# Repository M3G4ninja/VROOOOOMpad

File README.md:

### VROOOOMpad

VROOOOMpad is a 9-key macropad with a rotary encoder, an OLED Display. It also has 16 SK6812 LEDs, and uses KMK firmware.

It contains an implementation of every common part, and achieves my goal of being able to understand and use some of the comon inputs and outputs associated with a macropad.

**Features:**

-   Designed for a custom 3D printed case.
    
-   128x32 OLED Display
    
-   EC11 Rotary encoder for whatever you want
    
-   16 SK6812 RGB LEDs for per-key lighting and effects.
    
-   9 Keys in a 3x3 matrix to save on controller pins.
    
-   KMK support! 

**CAD Model:**  
The PCB is designed to show off my first ever pcb build. This has been a long journey and I am quite proud of my pcb.

**PCB**  
Here's my PCB! It was made in KiCad.

**Schematic**  

**PCB Layout**  

I used MX-style footprints for the keyswitches. A key design feature is the 3x3 key matrix using 1N4148 diodes, which allows 9 keys to be read using only 6 GPIO pins.

**Firmware Overview**  
This hackpad uses KMK firmware for everything.

-   The rotary encoder changes volume.
    
-   The 9 keys are set up with multiple layers for different shortcut menus and macros.
    
-   The OLED displays the currently active layer.

I might add more complex macros and lighting effects in the future! That's it for now.

**BOM:**  
Everything you need to make this hackpad.

-   9x Cherry MX Switches (or clones)
    
-   9x Keycaps
        
-   9x 1N4148 DO-35 Diodes
    
-   16x SK6812 5050 LEDs
    
-   1x 0.91" 128x32 I2C OLED Display
    
-   1x EC11 Rotary Encoder
    
-   1x Seeed Studio XIAO RP2040
    
-   1x Case

**Extra stuff**  
Get through work as fast as 1..2..VROOOOOM. Just as fast as a Twin Turbo 1st Gen Audi R8 V10
Time to get off the starting line and tune your VROOOOMpad to redline your productivity.

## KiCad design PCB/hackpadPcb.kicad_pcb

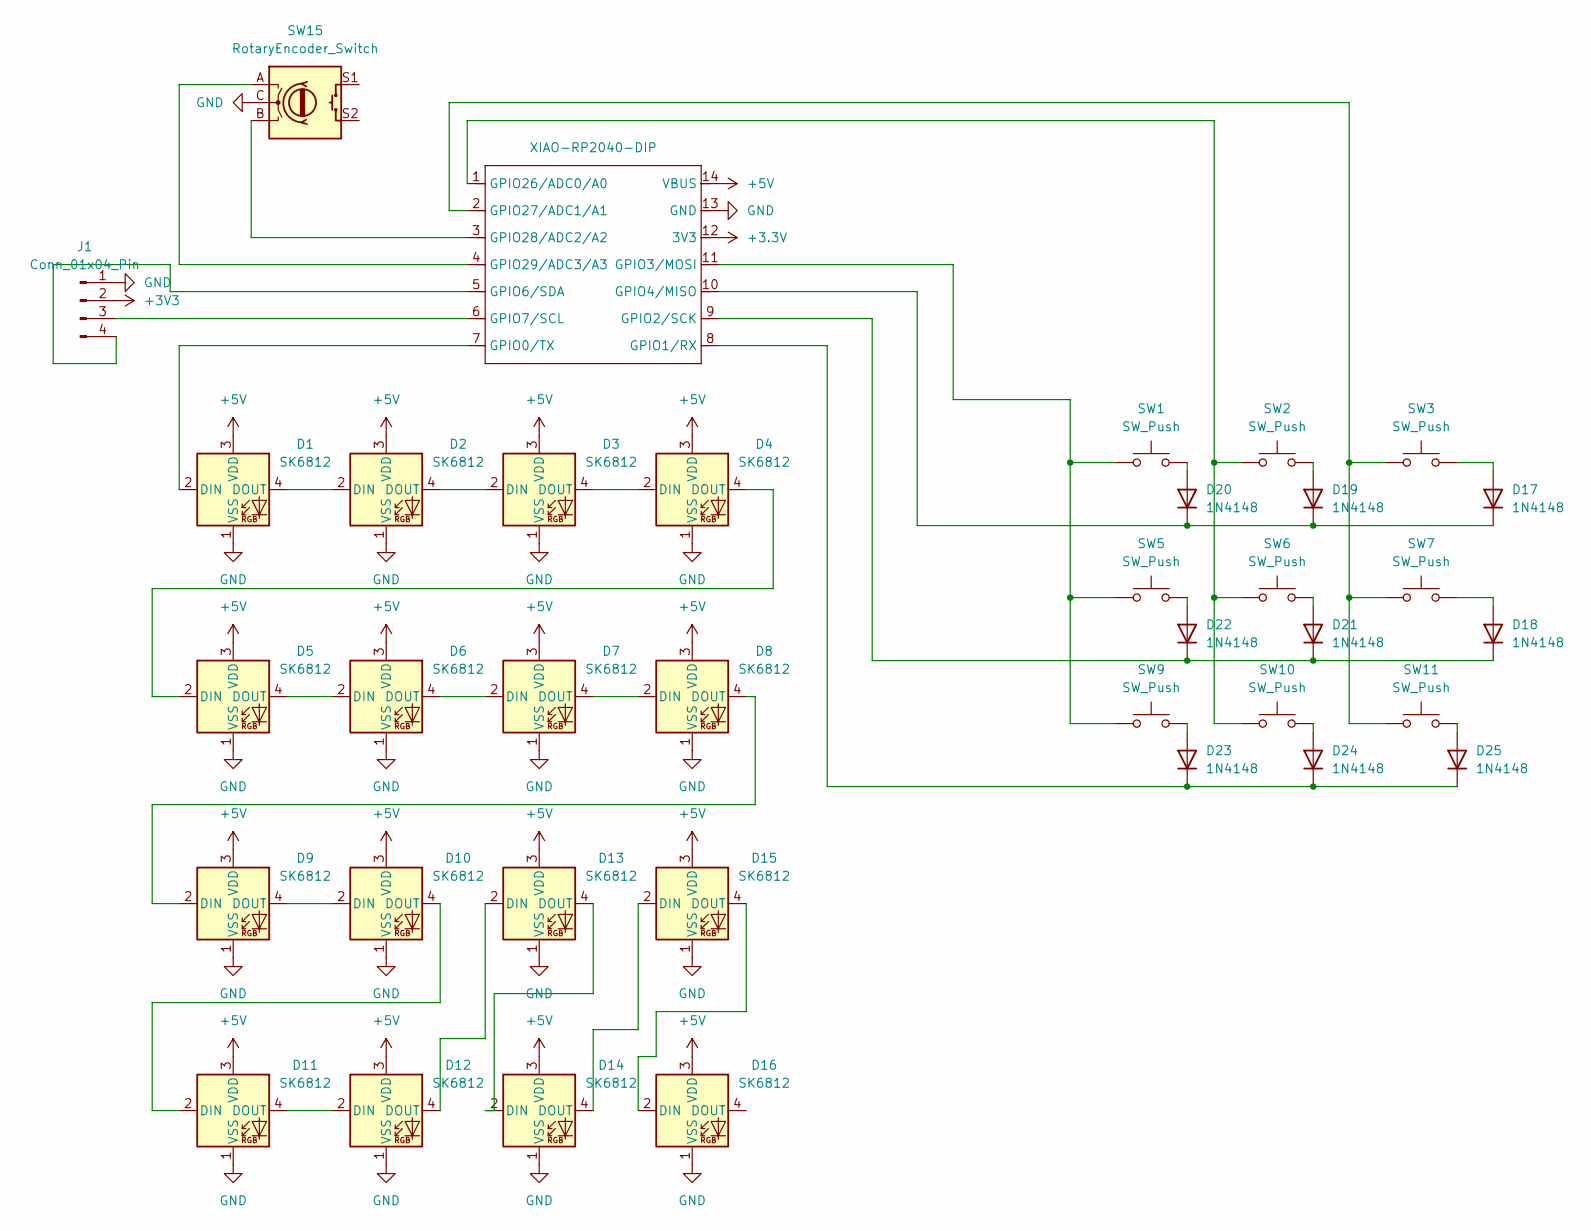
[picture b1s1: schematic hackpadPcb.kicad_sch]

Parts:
D1, D2, D3, D4, D5, D6, D7, D8, D9, D10, D11, D12, D13, D14, D15, D16: SK6812; LED_SK6812_PLCC4_5.0x5.0mm_P3.2mm
D17, D18, D19, D20, D21, D22, D23, D24, D25: 1N4148; D_DO-35_SOD27_P7.62mm_Horizontal
J1: Conn_01x04_Pin; SSD1306-0.91-OLED-4pin-128x32
SW1, SW2, SW3, SW5, SW6, SW7, SW9, SW10, SW11: SW_Push; SW_Cherry_MX_1.00u_PCB
SW15: RotaryEncoder_Switch; RotaryEncoder_Alps_EC11E-Switch_Vertical_H20mm
U2: XIAO-RP2040-DIP

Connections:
+3.3V: U2.12 (3V3)
+3V3: J1.2
+5V: D1.3 (VDD), D2.3 (VDD), D3.3 (VDD), D4.3 (VDD), D5.3 (VDD), D6.3 (VDD), D7.3 (VDD), D8.3 (VDD), D9.3 (VDD), D10.3 (VDD), D11.3 (VDD), D12.3 (VDD), D13.3 (VDD), D14.3 (VDD), D15.3 (VDD), D16.3 (VDD), U2.14 (VBUS)
GND: D1.1 (VSS), D2.1 (VSS), D3.1 (VSS), D4.1 (VSS), D5.1 (VSS), D6.1 (VSS), D7.1 (VSS), D8.1 (VSS), D9.1 (VSS), D10.1 (VSS), D11.1 (VSS), D12.1 (VSS), D13.1 (VSS), D14.1 (VSS), D15.1 (VSS), D16.1 (VSS), J1.1, SW15.C, U2.13 (GND)
unnamed: D1.2 (DIN), U2.7 (GPIO0/TX)
unnamed: D1.4 (DOUT), D2.2 (DIN)
unnamed: D2.4 (DOUT), D3.2 (DIN)
unnamed: D3.4 (DOUT), D4.2 (DIN)
unnamed: D4.4 (DOUT), D5.2 (DIN)
unnamed: D5.4 (DOUT), D6.2 (DIN)
unnamed: D6.4 (DOUT), D7.2 (DIN)
unnamed: D7.4 (DOUT), D8.2 (DIN)
unnamed: D8.4 (DOUT), D9.2 (DIN)
unnamed: D9.4 (DOUT), D10.2 (DIN)
unnamed: D10.4 (DOUT), D11.2 (DIN)
unnamed: D11.4 (DOUT), D12.2 (DIN)
unnamed: D12.4 (DOUT), D13.2 (DIN)
unnamed: D13.4 (DOUT), D14.2 (DIN)
unnamed: D14.4 (DOUT), D15.2 (DIN)
unnamed: D15.4 (DOUT), D16.2 (DIN)
unnamed: D17.2 (A), SW3.2
unnamed: D17.1 (K), D19.1 (K), D20.1 (K), U2.10 (GPIO4/MISO)
unnamed: D18.2 (A), SW7.2
unnamed: D18.1 (K), D21.1 (K), D22.1 (K), U2.9 (GPIO2/SCK)
unnamed: D19.2 (A), SW2.2
unnamed: D20.2 (A), SW1.2
unnamed: D21.2 (A), SW6.2
unnamed: D22.2 (A), SW5.2
unnamed: D23.2 (A), SW9.2
unnamed: D23.1 (K), D24.1 (K), D25.1 (K), U2.8 (GPIO1/RX)
unnamed: D24.2 (A), SW10.2
unnamed: D25.2 (A), SW11.2
unnamed: J1.3, U2.6 (GPIO7/SCL)
unnamed: J1.4, U2.5 (GPIO6/SDA)
unnamed: SW1.1, SW5.1, SW9.1, U2.11 (GPIO3/MOSI)
unnamed: SW2.1, SW6.1, SW10.1, U2.1 (GPIO26/ADC0/A0)
unnamed: SW3.1, SW7.1, SW11.1, U2.2 (GPIO27/ADC1/A1)
unnamed: SW15.B, U2.3 (GPIO28/ADC2/A2)
unnamed: SW15.A, U2.4 (GPIO29/ADC3/A3)

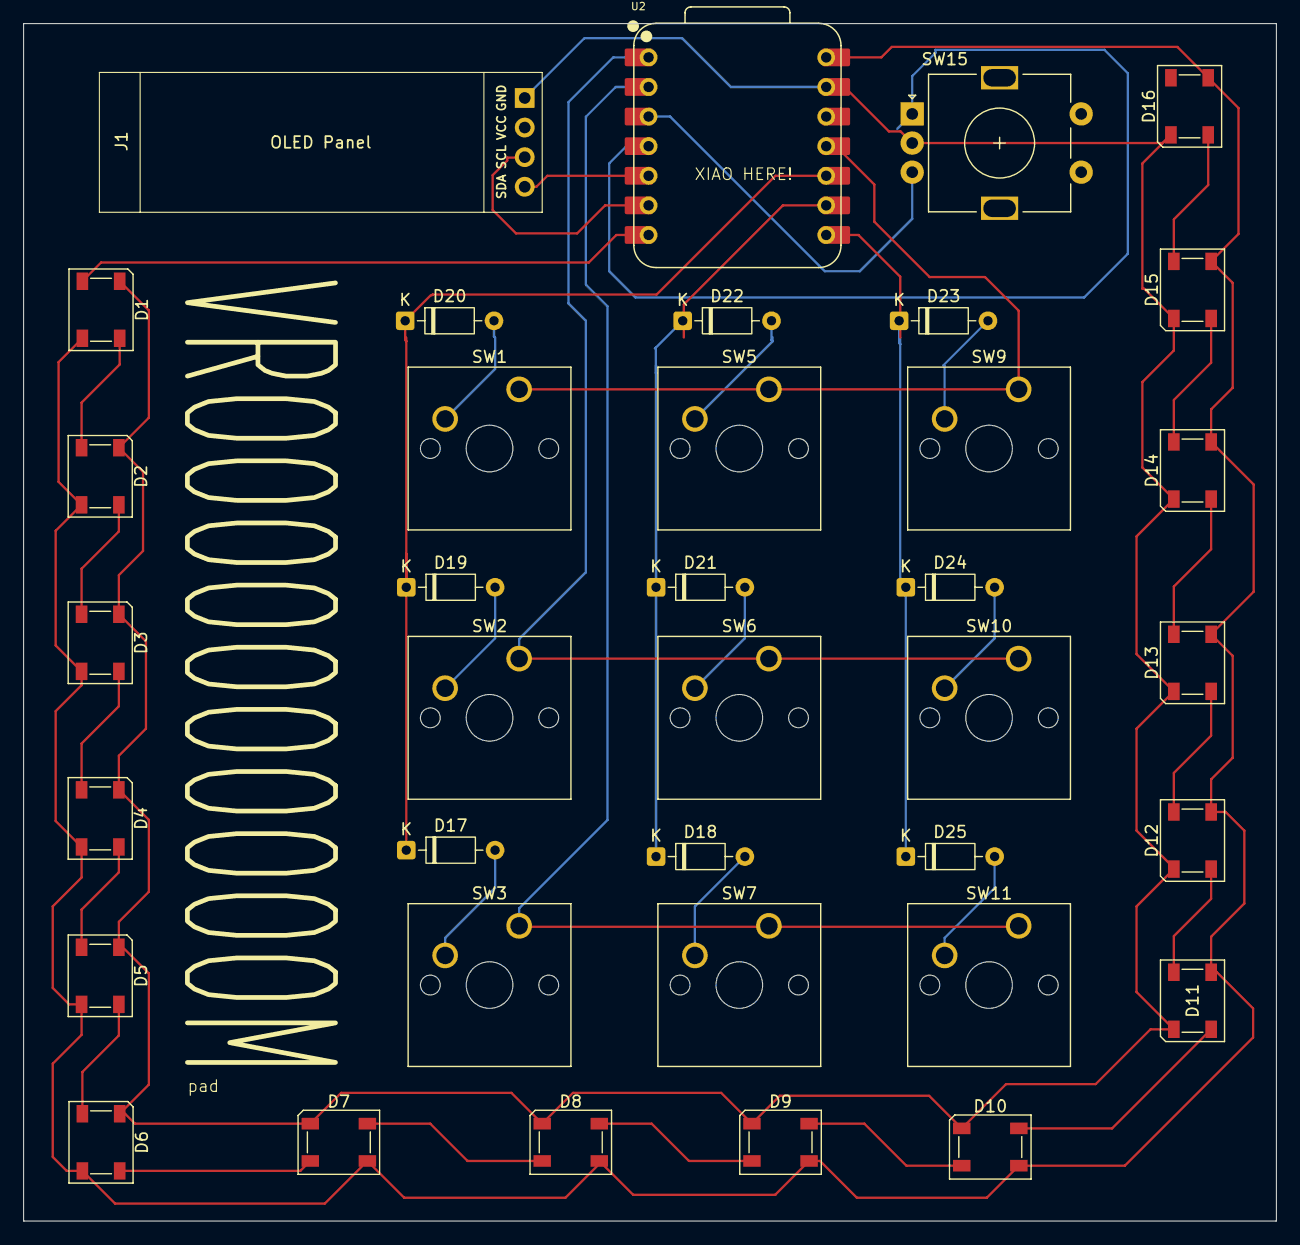
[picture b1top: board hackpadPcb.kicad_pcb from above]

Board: 2 copper layers, 107.5 x 102.8 mm, 37 parts (0 on the bottom side), 37 nets.

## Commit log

2025-08-01 Create d
2025-08-01 Create
2025-08-01 Create yum
2025-08-01 Rename Screenshot 2025-07-31 194310.png to CADpic
2025-08-01 Rename Screenshot 2025-07-31 194316.png to PCBpic
2025-08-01 Rename Screenshot 2025-07-31 194328.png to SchemPic
2025-08-04 fixed bottom and top
2025-08-04 Update README.md
    clean up all some of the fluff
2025-08-08 yea assembly now
